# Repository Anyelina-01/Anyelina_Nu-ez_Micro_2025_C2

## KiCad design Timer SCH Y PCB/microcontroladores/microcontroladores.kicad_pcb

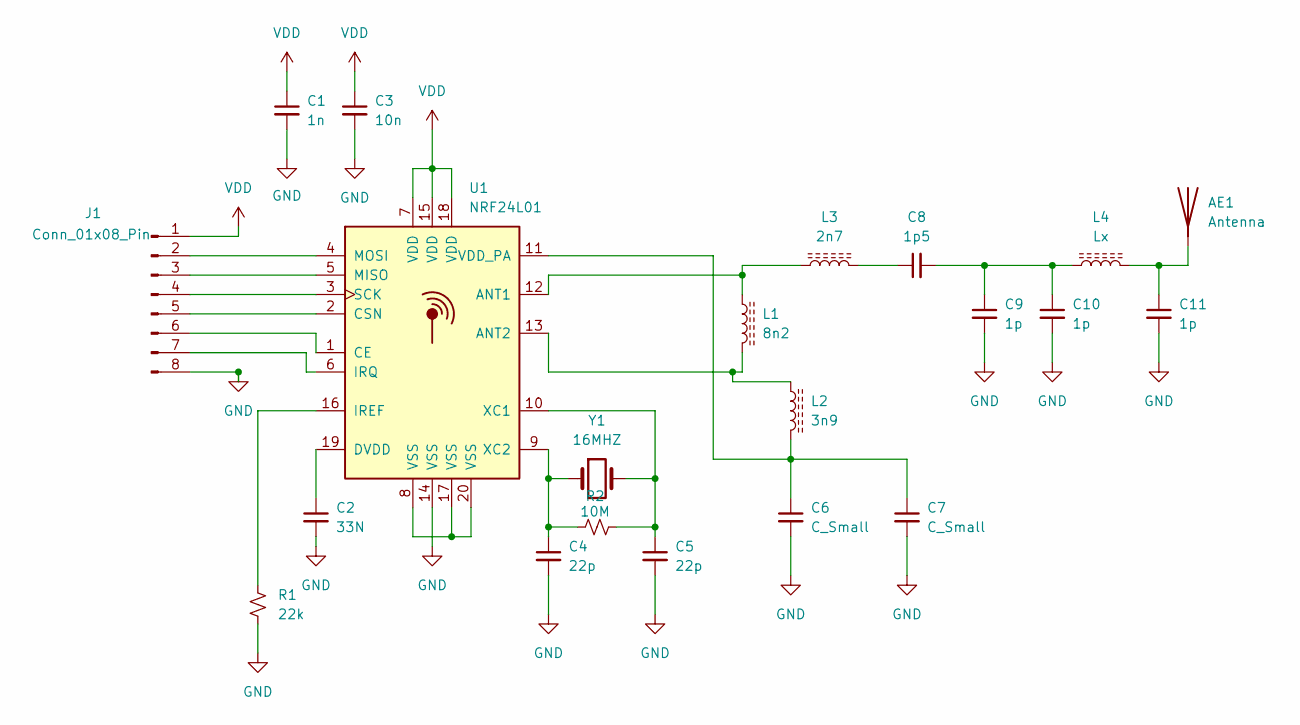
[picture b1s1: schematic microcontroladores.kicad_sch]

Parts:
AE1: Antenna; Texas_SWRA117D_2.4GHz_Right
C1: 1n; C_0402_1005Metric
C2: 33N; C_0402_1005Metric
C3: 10n; C_0402_1005Metric
C4, C5: 22p; C_0402_1005Metric
C6, C7: C_Small; C_0402_1005Metric
C8: 1p5; C_0402_1005Metric
C9, C10, C11: 1p; C_0402_1005Metric
J1: Conn_01x08_Pin; Hirose_DF13-08P-1.25DSA_1x08_P1.25mm_Vertical
L1: 8n2; L_0402_1005Metric
L2: 3n9; L_0402_1005Metric
L3: 2n7; L_0402_1005Metric
L4: Lx; L_0402_1005Metric
R1: 22k; R_0402_1005Metric
R2: 10M; R_0402_1005Metric
U1: NRF24L01; QFN-20-1EP_4x4mm_P0.5mm_EP2.5x2.5mm
Y1: 16MHZ; Crystal_SMD_3215-2Pin_3.2x1.5mm

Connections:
GND: C1.2, C2.2, C3.2, C4.2, C5.2, C6.2, C7.2, C9.2, C10.2, C11.2, J1.8, R1.2, U1.14 (VSS)
unnamed: AE1.1 (A), C11.1, L4.2
unnamed: C8.1, L3.2
unnamed: C8.2, C9.1, C10.1, L4.1
unnamed: J1.2, U1.4 (MOSI)
unnamed: J1.3, U1.5 (MISO)
unnamed: J1.4, U1.3 (SCK)
unnamed: J1.5, U1.2 (CSN)
unnamed: J1.6, U1.1 (CE)
unnamed: J1.7, U1.6 (IRQ)
unnamed: L1.1, L3.1, U1.12 (ANT1)
unnamed: L1.2, L2.1, U1.13 (ANT2)
unnamed: C2.1, U1.19 (DVDD)
unnamed: R1.1, U1.16 (IREF)
unnamed: C6.1, C7.1, L2.2, U1.11 (VDD_PA)
unnamed: U1.8 (VSS), U1.17 (VSS), U1.20 (VSS)
unnamed: C5.1, R2.2, U1.10 (XC1), Y1.2
unnamed: C4.1, R2.1, U1.9 (XC2), Y1.1
VDD: C1.1, C3.1, J1.1, U1.7 (VDD), U1.15 (VDD), U1.18 (VDD)

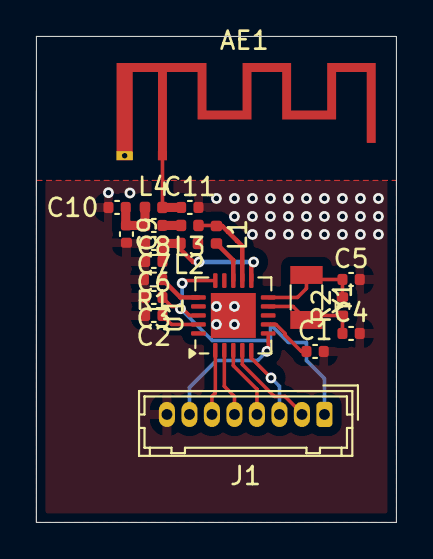
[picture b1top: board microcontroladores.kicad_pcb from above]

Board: 2 copper layers, 20.0 x 27.0 mm, 21 parts (0 on the bottom side), 19 nets.

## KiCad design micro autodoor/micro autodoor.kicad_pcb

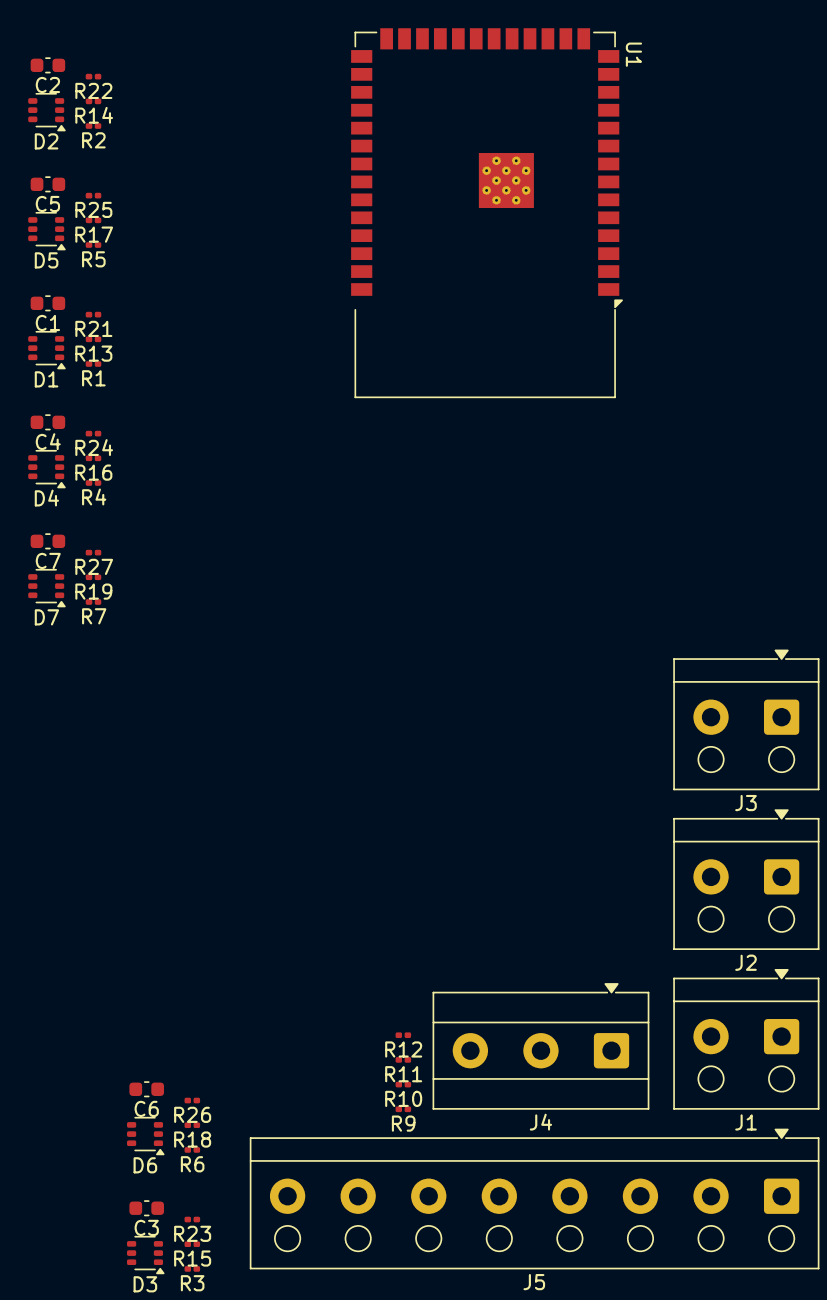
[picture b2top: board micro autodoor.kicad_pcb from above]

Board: 2 copper layers, 45 parts (0 on the bottom side), 16 nets, no tracks yet.

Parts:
C1, C2, C3, C4, C5, C6, C7: 100nF; C_0603_1608Metric
D1, D2, D3, D4, D5, D6, D7: PESD3V3L5UY; SOT-363_SC-70-6
J1, J2, J3: Screw_Terminal_01x02; TerminalBlock_RND_205-00001_1x02_P5.00mm_Horizontal
J4: Screw_Terminal_01x03; TerminalBlock_MetzConnect_Type055_RT01503HDWU_1x03_P5.00mm_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
J5: Screw_Terminal_01x08; TerminalBlock_RND_205-00007_1x08_P5.00mm_Horizontal
R1, R2, R3, R4, R5, R6, R7, R21, R22, R23, R24, R25, R26, R27: 10k; R_0201_0603Metric
R9, R10, R11, R12: 22K; R_0201_0603Metric
R13, R14, R15, R16, R17, R18, R19: 100; R_0201_0603Metric
U1: ESP32-S3-WROOM-1

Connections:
+3.3V: R1.1, R2.1, R3.1, R4.1, R5.1, R6.1, R7.1, R9.1, R10.1, R11.1, R12.1, U1.2 (3V3)
/board_principal/BA: J5.4, R4.2, R16.2
/board_principal/BC: J5.3, R5.2, R17.2
/board_principal/B_STOP: J5.2, R6.2, R18.2
/board_principal/FTC: J5.1, R7.2, R19.2
/board_principal/IMPUT_DIGITAL1/IN: R2.2, R14.2
/board_principal/IMPUT_DIGITAL1/OUT: C2.1, D2.1 (K1), R14.1, R22.1
/board_principal/IMPUT_DIGITAL2/OUT: C3.1, D3.1 (K1), R15.1, R23.1
/board_principal/IMPUT_DIGITAL3/OUT: C4.1, D4.1 (K1), R16.1, R24.1
/board_principal/IMPUT_DIGITAL4/OUT: C5.1, D5.1 (K1), R17.1, R25.1
/board_principal/IMPUT_DIGITAL5/OUT: C6.1, D6.1 (K1), R18.1, R26.1
/board_principal/IMPUT_DIGITAL6/OUT: C7.1, D7.1 (K1), R19.1, R27.1
/board_principal/IMPUT_DIGITAL/IN: R1.2, R13.2
/board_principal/IMPUT_DIGITAL/OUT: C1.1, D1.1 (K1), R13.1, R21.1
/board_principal/PP: J5.5, R3.2, R15.2
GND: C1.2, C2.2, C3.2, C4.2, C5.2, C6.2, C7.2, D1.2 (A), D2.2 (A), D3.2 (A), D4.2 (A), D5.2 (A), D6.2 (A), D7.2 (A), J3.2, J4.2, J5.8, R21.2, R22.2, R23.2, R24.2, R25.2, R26.2, R27.2, U1.1 (GND), U1.40 (GND), U1.41 (GND)

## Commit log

2025-06-27 Maquina De Estado
2025-07-03 Create tem
